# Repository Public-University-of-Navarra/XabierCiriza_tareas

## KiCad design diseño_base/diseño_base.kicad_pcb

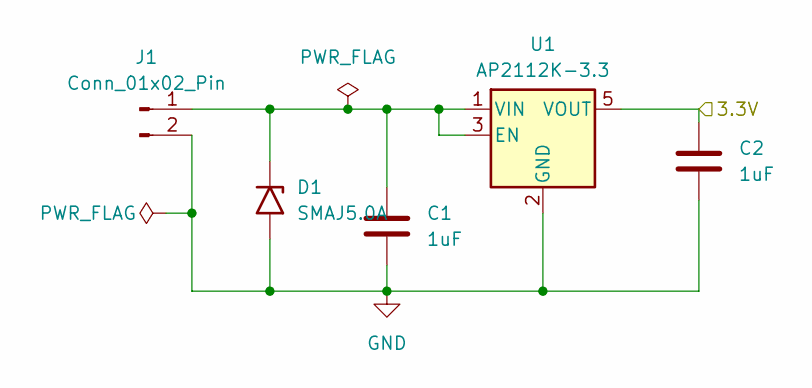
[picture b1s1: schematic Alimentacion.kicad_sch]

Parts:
C1, C2: 1uF; C_0603_1608Metric
D1: SMAJ5.0A; D_SMA
J1: Conn_01x02_Pin; PinHeader_1x02_P2.54mm_Vertical
U1: AP2112K-3.3; SOT-23-5

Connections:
/Microcontrolador/3.3V: C2.1, U1.5 (VOUT); also elsewhere on the board
GND: C1.2, C2.2, D1.2 (A2), J1.2, U1.2 (GND); also elsewhere on the board
unnamed: C1.1, D1.1 (A1), J1.1, U1.1 (VIN), U1.3 (EN)

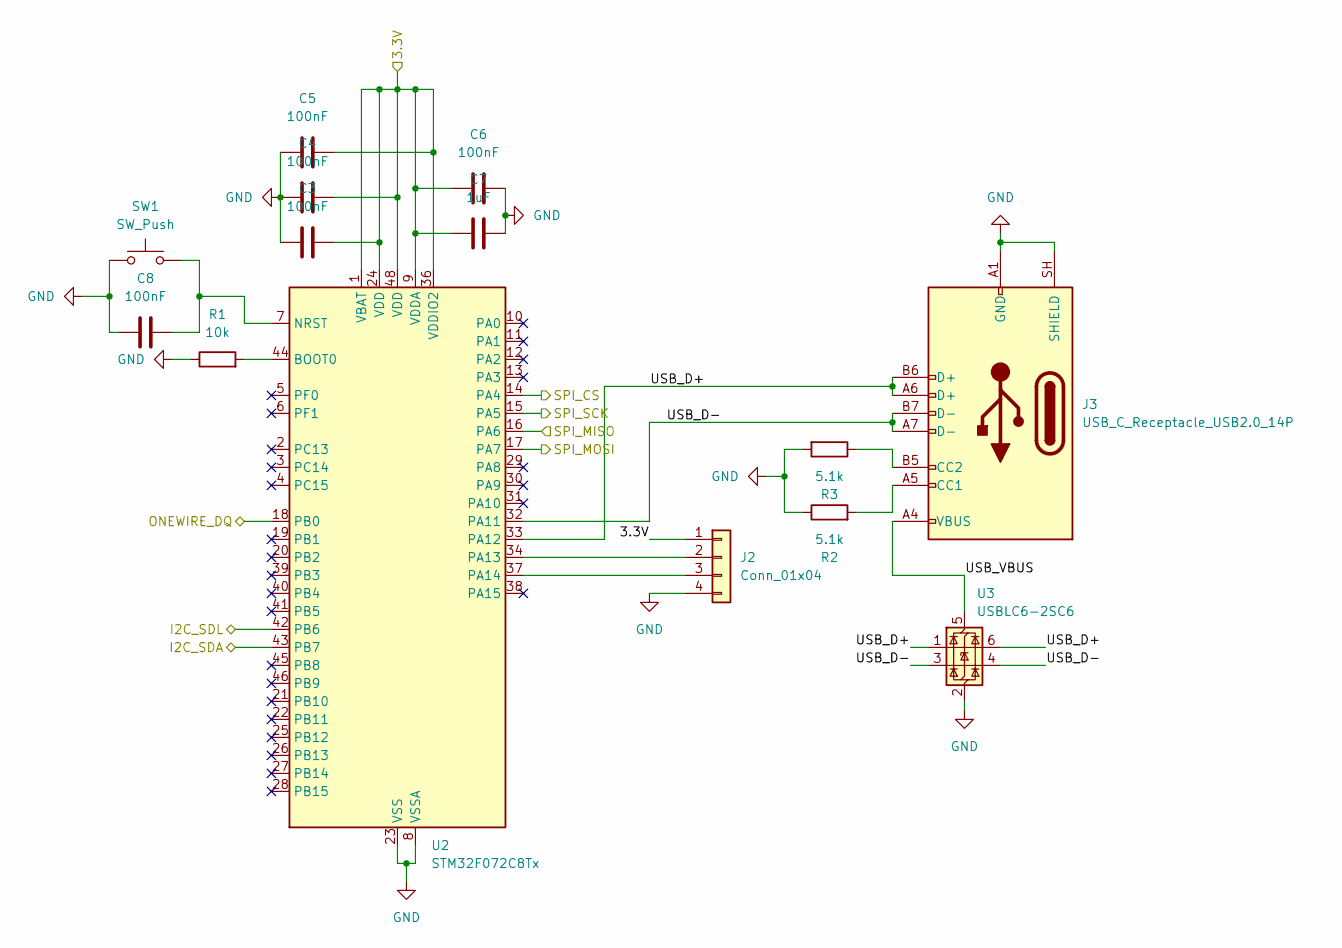
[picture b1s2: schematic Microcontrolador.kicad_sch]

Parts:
C3, C4, C5, C6, C8: 100nF; C_0603_1608Metric
C7: 1uF; C_0603_1608Metric
J2: Conn_01x04; PinHeader_1x04_P2.54mm_Vertical
J3: USB_C_Receptacle_USB2.0_14P; USB_C_Receptacle_Molex_21698900x1
R1: 10k; R_0603_1608Metric
R2, R3: 5.1k; R_0603_1608Metric
SW1: SW_Push; SW_PUSH_6mm_H5mm
U2: STM32F072C8Tx; LQFP-48_7x7mm_P0.5mm
U3: USBLC6-2SC6; SOT-23-6

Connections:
/Microcontrolador/3.3V: C3.1, C4.1, C5.1, C6.1, C7.1, J2.1, U2.1 (VBAT), U2.9 (VDDA), U2.24 (VDD), U2.36 (VDDIO2), U2.48 (VDD); also elsewhere on the board
/Microcontrolador/I2C_SDA: U2.43 (PB7); also elsewhere on the board
/Microcontrolador/I2C_SDL: U2.42 (PB6); also elsewhere on the board
/Microcontrolador/ONEWIRE_DQ: U2.18 (PB0); also elsewhere on the board
/Microcontrolador/SPI_CS: U2.14 (PA4); also elsewhere on the board
/Microcontrolador/SPI_MISO: U2.16 (PA6); also elsewhere on the board
/Microcontrolador/SPI_MOSI: U2.17 (PA7); also elsewhere on the board
/Microcontrolador/SPI_SCK: U2.15 (PA5); also elsewhere on the board
/Microcontrolador/USB_D+: J3.A6 (D+), J3.B6 (D+), U2.33 (PA12), U3.1 (I/O1), U3.6 (I/O1)
/Microcontrolador/USB_D-: J3.A7 (D-), J3.B7 (D-), U2.32 (PA11), U3.3 (I/O2), U3.4 (I/O2)
/Microcontrolador/USB_VBUS: J3.A4 (VBUS), J3.A9 (VBUS), J3.B4 (VBUS), J3.B9 (VBUS), U3.5 (VBUS)
GND: C3.2, C4.2, C5.2, C6.2, C7.2, C8.2, J2.4, J3.A1 (GND), J3.A12 (GND), J3.B1 (GND), J3.B12 (GND), J3.SH (SHIELD), R1.1, R2.1, R3.2, SW1.1, U2.8 (VSSA), U2.23 (VSS), U2.35 (VSS), U2.47 (VSS), U3.2 (GND); also elsewhere on the board
unnamed: J2.2, U2.34 (PA13)
unnamed: J2.3, U2.37 (PA14)
unnamed: J3.A5 (CC1), R2.2
unnamed: J3.B5 (CC2), R3.1
unnamed: R1.2, U2.44 (BOOT0)
unnamed: C8.1, SW1.2, U2.7 (NRST)

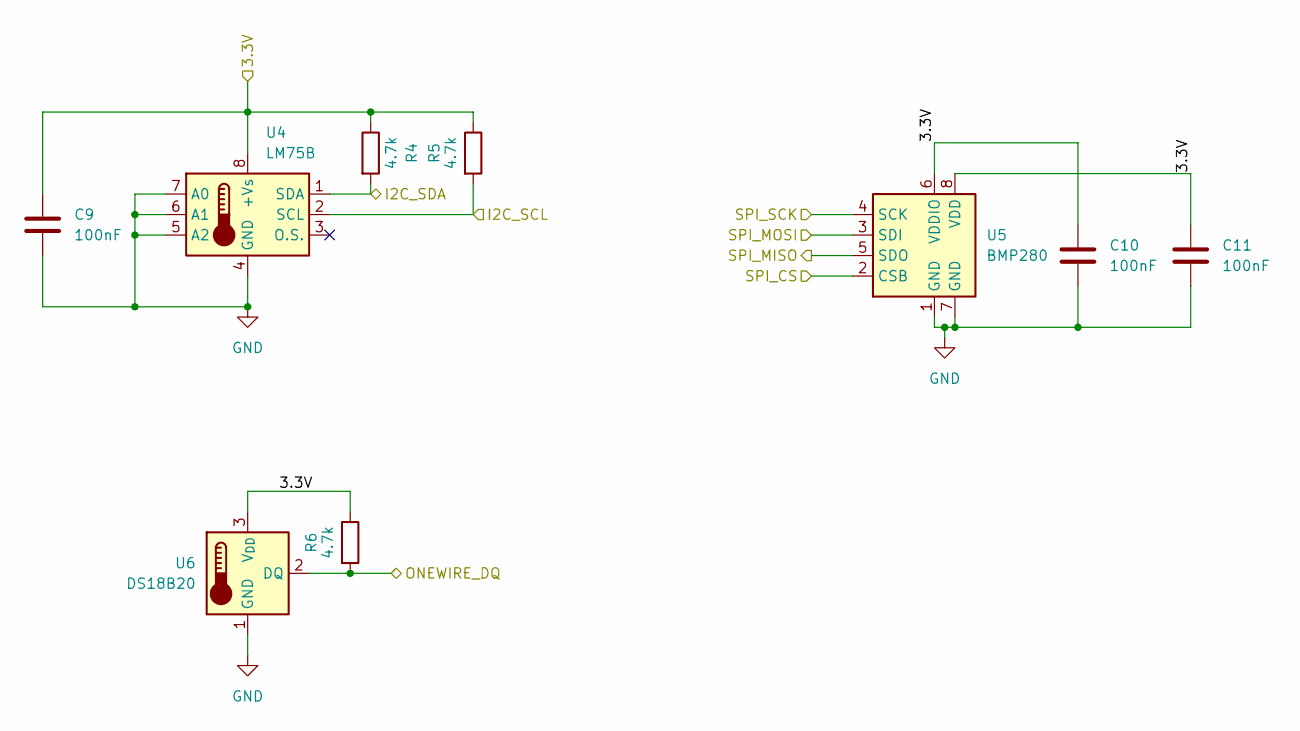
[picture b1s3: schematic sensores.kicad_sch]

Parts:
C9, C10, C11: 100nF; C_0603_1608Metric
R4, R5, R6: 4.7k; R_0603_1608Metric
U4: LM75B; SOIC-8_3.9x4.9mm_P1.27mm
U5: BMP280; Bosch_LGA-8_2x2.5mm_P0.65mm_ClockwisePinNumbering
U6: DS18B20; TO-92_Inline

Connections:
/Microcontrolador/3.3V: C9.1, C10.1, C11.1, R4.1, R5.1, R6.1, U4.8 (+Vs), U5.6 (VDDIO), U5.8 (VDD), U6.3 (V_{DD}); also elsewhere on the board
/Microcontrolador/I2C_SDA: R4.2, U4.1 (SDA); also elsewhere on the board
/Microcontrolador/I2C_SDL: R5.2, U4.2 (SCL); also elsewhere on the board
/Microcontrolador/ONEWIRE_DQ: R6.2, U6.2 (DQ); also elsewhere on the board
/Microcontrolador/SPI_CS: U5.2 (CSB); also elsewhere on the board
/Microcontrolador/SPI_MISO: U5.5 (SDO); also elsewhere on the board
/Microcontrolador/SPI_MOSI: U5.3 (SDI); also elsewhere on the board
/Microcontrolador/SPI_SCK: U5.4 (SCK); also elsewhere on the board
GND: C9.2, C10.2, C11.2, U4.4 (GND), U4.5 (A2), U4.6 (A1), U4.7 (A0), U5.1 (GND), U5.7 (GND), U6.1 (GND); also elsewhere on the board

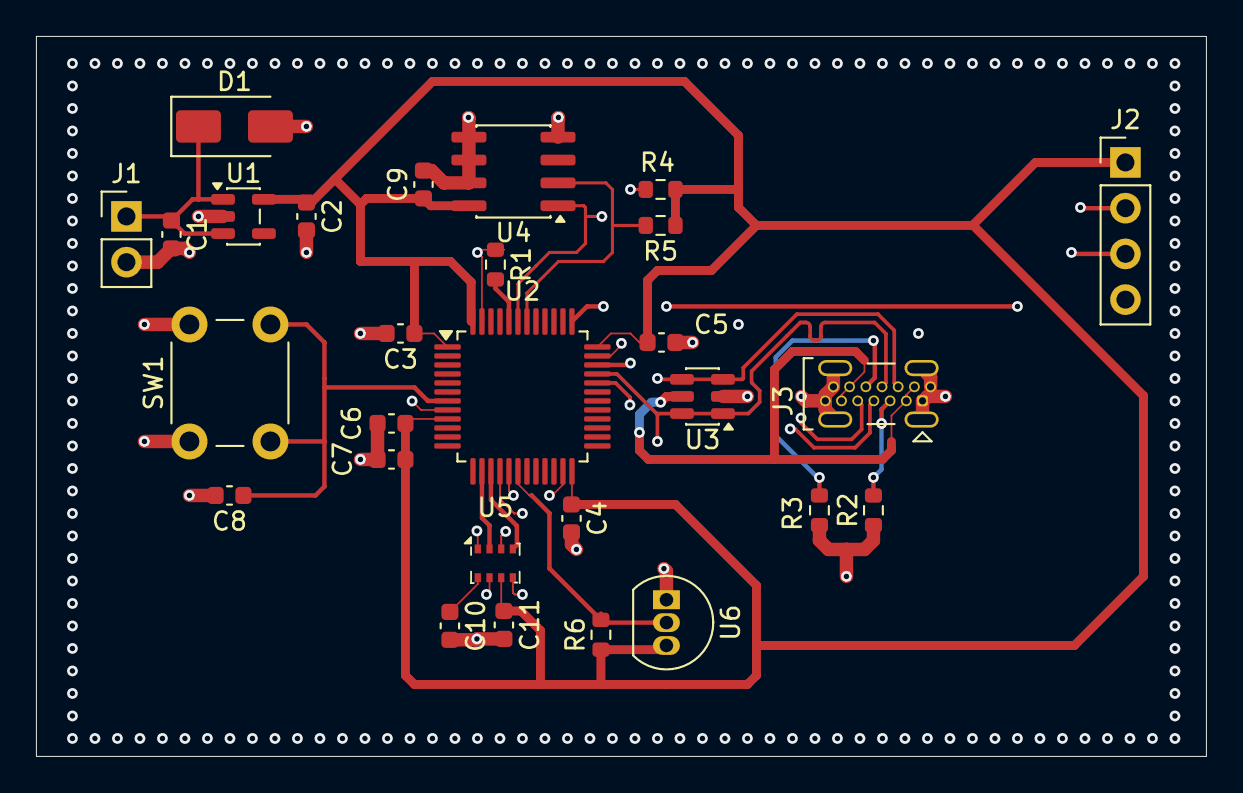
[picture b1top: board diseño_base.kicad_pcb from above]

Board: 4 copper layers, 65.0 x 40.0 mm, 28 parts (0 on the bottom side), 19 nets.
